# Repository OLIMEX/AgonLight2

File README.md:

# AgonLight2

AgonLight OSHW Retro Z80 computer - an updated version with few updates

This is a re-design of the original version of AgonLight made by Bernardo Kastrup: https://github.com/TheByteAttic/AgonLight

What is new:
- The board schematic and PCB were re-captured and re-layout in KiCad instead of EasyEDA, KiCad is open source software – free to download and use, it is a more fitting CAD tool for an Open Source Hardware project;
- The power of the original AgonLight is delivered through USB-A connector. We decided to replace it with USB-C connector which is used in all new phones, tablets, and devices due to the new EU directive. Usually everyone has such a cable at home to charge and transfer files to their cell phone;
- The linear voltage regulator is replaced with DCDC which delivers up to 2A current;
- Battery Li-Po charger and step-up converter were added, this keeps the board fully operational even if the external power supply gets disconnected;
- The original design has a PS2 connector for a keyboard and required a USB to PS2 adapter to operate with the more available USB keyboards. We replaced the PS2 connector with a USB-A connector so a normal USB keyboard (which supports PS2) can be directly plugged-in to AgonLight;
- AS7C34096A-10TCTR SRAM is routed with 40 ohm impedance lines as per the datasheet;
- Fixed a signal naming in the ESP32-PICO-D4, which now is updated in the original AgonLight documentation;
- The bare header 32-pin connector is replaced with a plastic boxed 34-pin connector following the same layout and adding two additional signals Vbat and Vin which allow AgonLight to be powered via this connector too;
- [UEXT connector](https://www.olimex.com/Products/Modules/UEXT/) was added - it allows AgonLight to be expanded easily (without soldering) with: [temperature sensors, environmental air quality sensors, pressure sensors, humidity sensors, gyroscopes, light sensors, RS485, LCDs, LED matrices, relays, Bluetooth modules, Zigbee modules, Lora modules, GSM modules, RFID readers, GPS, pulse, EKG, RTC, etc](https://www.olimex.com/Products/Modules/);
- Added four 3.3mm mount holes with GND sleeve were added so the board can be attached firmly to a box or another board but also kept the original 2.5mm mount holes.

Please do not forget to check AgonLight topics in GitHub for many utilities and code written by AgonLight community: https://github.com/topics/agon-light

## Useful Agon Resources
- Bernardo Kastrup https://github.com/TheByteAttic/AgonLight
- Dean Belfield Agon VDP, MOS, BBC-BASIC, Agon DOCs, projects https://github.com/breakintoprogram
- Lennart Benschop FORTH, Nano editor and MOS utilities https://github.com/lennart-benschop
- Jeroen Venema Agon Flash, HexLoad, Z80 assembler, tools, sokoban game https://github.com/envenomator
- Mario Smit Agon ZDI Load and tools https://github.com/S0urceror
- Reinhard Schu Agon Assembly https://github.com/schur/Agon-Light-Assembly
- AgonLight emulator https://github.com/james7780/AgonLightEmuSDL
- Alexander Sharikhin MOS tools https://github.com/nihirash/Agon-MOS-Tools
- Nicholas Pratt Agon Game https://github.com/NicholasPratt/Nova-Star
- Robert Lowe Agon Games collection https://github.com/pngwen
- LuzrBum Agon Games https://github.com/LuzrBum

## Licensee
* Hardware is released under CERN Open Hardware Licence Version 2 - Strongly Reciprocal, all silkscreen credits to Bernardo Kastrup and Dean Belfield should remain;
* Software is released under zlib Licensee
* Documentation is released under CC BY-SA 3.0

## Change History

23-04-2023 - Add Resources

14-12-2022 - Initial upload  of CAD files for first prototypes

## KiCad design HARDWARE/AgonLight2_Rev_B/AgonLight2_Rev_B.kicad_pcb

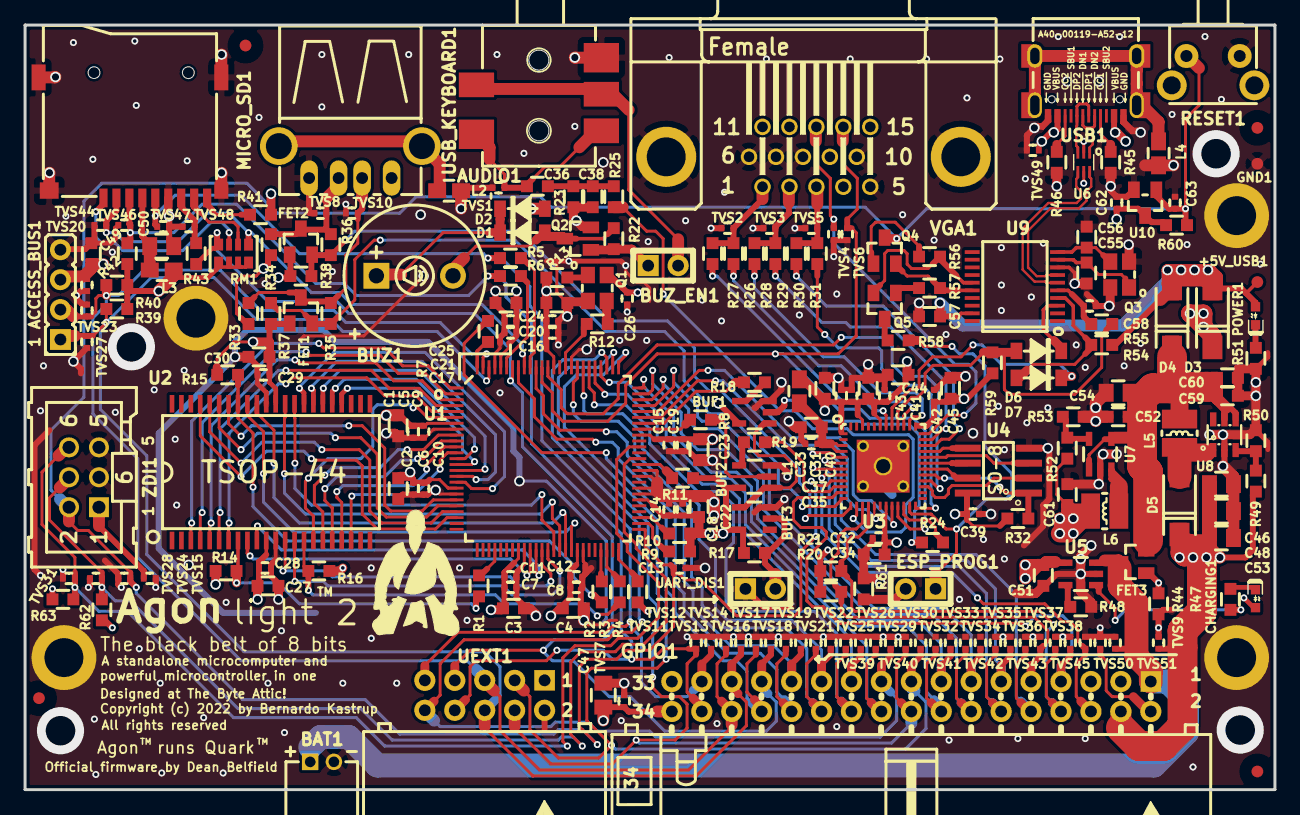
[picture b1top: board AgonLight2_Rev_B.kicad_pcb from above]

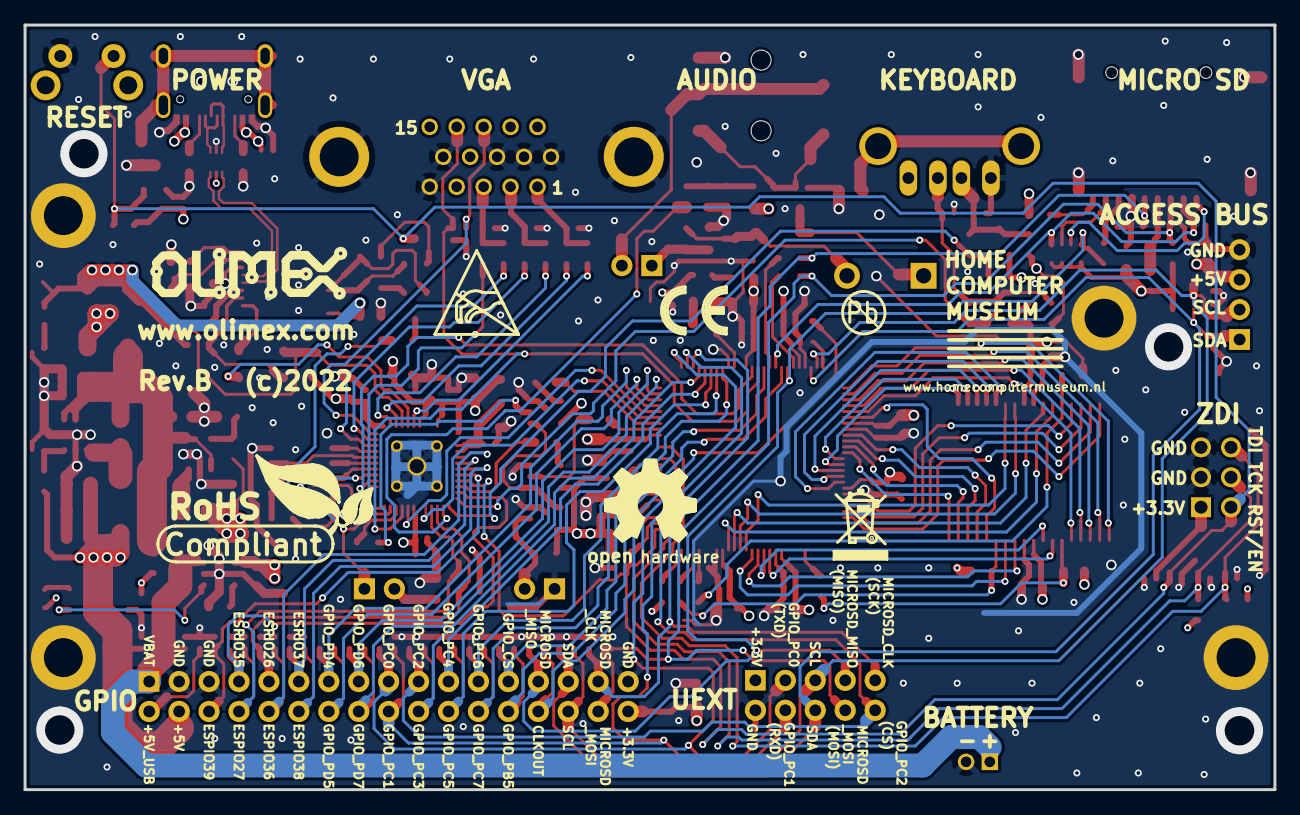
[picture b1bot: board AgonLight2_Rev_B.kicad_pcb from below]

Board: 4 copper layers, 106.1 x 64.9 mm, 247 parts (8 on the bottom side), 157 nets.

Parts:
+5V_USB1: TESTPAD; TP_SMD
ACCESS_BUS1: HN1x4
AUDIO1: PJ-3.5-365-5P(SCJ325P00XG0B02G)-COPY; SCJ325P00XG0B02G
BAT1: DW02R; LIPO_BAT-CON2DW02R
BUF1, BUF2: SN74LVC1G125DBVR; SOT-23-5
BUF3: SN74LVC1G04DBVR(SOT23-5); SOT-23-5
BUZ1: BUZZER_PB1221P(1.1-1.7V_2kHz_12MM); PB1221P_1-Plus_2-Minus
BUZ_EN1: HN1x2+MJ6; HN1x2_Jumper
C1, C2, C3, C4, C22, C23, C24, C25, C27, C30, C33, C34, C36, C37, C43, C44, C45, C49, C59, C60: 10uF/6.3V/20%/X5R/0603; C_0603_5MIL_DWS
C5, C6, C7, C8, C13, C18, C19, C20, C21, C26, C28, C29, C31, C32, C35, C39, C40, C41, C42, C58, C62, C63: 100nF/10V/20%/X5R/0402; C_0402_5MIL_DWS
C9, C10, C11, C12, C14, C15, C16, C17: 1nF/X7R/50VDC/0402; C_0402_5MIL_DWS
C38: 33nF/X7R/50VDC/10%/0603; C_0603_5MIL_DWS
C46, C47, C48, C50, C53, C54: 47uF/6.3V/20%/X5R/0805; C_0805_5MIL_DWS
C51, C52, C57, C61: 22uF/6.3V/20%/X5R/C0603; C_0603_5MIL_DWS
C55, C56: 27pF/C0G/50VDC/5%/0603; C_0603_5MIL_DWS
CHARGING1: LED/YELLOW/0603; LED_0603_KA
D1, D2: 1N4148W/SOD123; SOD-123_1C-2A_KA
D3: NA; SMA-KA
D4, D5: 1N5822/SS34/SMA; SMA-KA
D6, D7: 1N5819S4/SOD123; SOD-123_1C-2A_KA
ESP_PROG1: HN1x2+MJ6; HN1x2_Jumper
FET1, FET2: BSS138(SOT23-3); SOT23
FET3: WPM2015-3/TR; SOT23
FID1, FID2, FID3, FID4: Fiducial; Fiducial1x3
GND1: TESTPAD; TP_SMD
GPIO1: B-R-34-LF(BH34R)2x17_90DEGREE; BH34R
HCM_LOGO: Sign; HomeComputerMuseum2
L1, L2, L3, L4: FB0805/600R/2A; L_0805_5MIL_DWS
L5, L6: 2.2uH/1.5A/NRS3015T2R2MNGH; CD32
Logo_OLIMEX_TB: Logo_OLIMEX_TB
MICRO_SD1: TFC-WPAPR-08-LF; TFC-WPAPR-08
Mounting_hole1, Mounting_hole2, Mounting_hole3, Mounting_hole4: Mounting_hole; Mounting_hole_3.3mm_with_5.5mm_pad
POWER1: LED/RED/0603; LED_0603_KA
Q1: ASE-18.432MHZ-L-C-T; Oscillator-18.432MHz-3.2x2.5mm
Q2, Q4, Q5: BC817-40NPN(SOT23); SOT23
Q3: Q12MHz/20pF/10ppm/4P/3.2x2.5mm; TSX-3.2x2.5mm_GND(3)
R1, R2, R3, R5, R6, R7, R8, R12, R18, R19, R24, R43: 33R/0603; R_0603_5MIL_DWS
R4, R9, R10, R11, R13, R14, R15, R16: 4.7K/0603; R_0603_5MIL_DWS
R17, R32, R33, R34, R42, R44, R54, R55, R60, R61, R62, R63: 10K/0603; R_0603_5MIL_DWS
R20, R21: 22K/0603; R_0603_5MIL_DWS
R22, R37, R38, R39, R40, R47, R48, R51, R56, R57: 2.2K/0603; R_0603_5MIL_DWS
R23: 150R/0603; R_0603_5MIL_DWS
R25: 270R/0603; R_0603_5MIL_DWS
R26, R28, R30: 430R/1%/0603; R_0603_5MIL_DWS
R27, R29, R31: 820R/0603; R_0603_5MIL_DWS
R35, R36: NA(120R/0603); R_0603_5MIL_DWS
R41, R59: NA; R_0603_5MIL_DWS
R45, R46: 5.1K/0603; R_0603_5MIL_DWS
R49: 8.2K/1%/0603; R_0603_5MIL_DWS
R50: 1.1K/1%/0603; R_0603_5MIL_DWS
R52: 220K/0603; R_0603_5MIL_DWS
R53: 49.9K/1%/0603; R_0603_5MIL_DWS
R58: 220R/0603; R_0603_5MIL_DWS
RESET1: B3F-3150; B3F-31XX
RM1: RA1206_(4x0603)_4B8_100k; RA1206_(4X0603)_4B8_xx
Sign_Antistatic: Sign_Antistatic
Sign_CE: CE_Sign
Sign_OSHW_8x8: Sign_OSHW_8x8
Sign_PB-Free: Sign_PB-Free
Sign_RecycleBin_1: Sign_RecycleBin_1
Sign_RoHS_1: Sign_RoHS_1
TVS1, TVS2, TVS3, TVS4, TVS5, TVS6, TVS7, TVS11, TVS12, TVS13, TVS14, TVS15, TVS16, TVS17, TVS18, TVS19, TVS20, TVS21, TVS22, TVS23, TVS24, TVS25, TVS26, TVS27, TVS28, TVS29, TVS30, TVS31, TVS32, TVS33, TVS34, TVS35, TVS36, TVS37, TVS38, TVS39, TVS40, TVS41, TVS42, TVS43, TVS44, TVS45, TVS46, TVS47, TVS48: NA; D_0402_5MIL_DWS
TVS8, TVS9, TVS10, TVS49, TVS50, TVS51: NA(GG0402052R542P); D_0402_5MIL_DWS
U1: EZ80F92AZ020EG(LQFP100); LQFP-100_14x14mm_STM32H730VBT6
U2: AS7C34096A-10TCTR; TSOP-44_Pitch-0.80mm_18.80x11.80x1.20mm
U3: ESP32-PICO-D4
U4: APS6404L-3SQR-SN; SO-8
U5: BL4054B-42TPRN(SOT23-5); SOT-23-5
U6: USBLC6-2P6; SOT-666
U7: SY8089AAAC(SOT23-5); SOT-23-5
U8: MT3608(SOT23-6); SOT23-6
U9: CH340T(SSOP20W); SSOP-20W
U10: VDA2710NTA(SOT-23); SOT-23
UART_DIS1: HN1x2+MJ6; HN1x2_Jumper
UEXT1: B-R-10-LF(BH10R)2x05_90DEGREE; UEXT_BH10R
USB1: USB-C-16P-F(A40-00119-A52-12); USB2.0_TYPE-C(A40-00119-A52-12)
USB_KEYBOARD1: USB-SRWH-4A-LF(USB-A); USB_PN87520_HOST_PTH
VGA1: VGA15; VGA15-F(CD0515S21J0)
ZDI1: BH06S_2x3(B-D-02x3-LF); BH06S

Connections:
+3.3V: BUF1.5, BUF2.5, BUF3.5, C1.1, C2.1, C3.1, C4.1, C5.1, C6.1, C7.1, C8.1, C9.1, C10.1, C11.1, C12.1, C14.1, C15.1, C16.1, C17.1, C18.1, C19.1, C20.1, C21.1, C22.1, C23.1, C24.1, C25.1, C26.1, C27.1, C28.1, C29.1, C30.1, C31.1, C32.1, C33.1, C34.1, C39.2, C40.1, C41.1, C42.1, C43.1, C44.1, C45.1, C47.2, C61.1, C62.1, D2.2, FET1.1, FET2.1, GPIO1.34, L1.1, L3.1, L6.2, Q1.4, R4.1, R9.1, R10.1, R11.1, R13.1, R14.1, R15.1, R16.1, R17.2, R20.1, R21.1, R32.2, R37.2, R38.2, R39.2, R40.2, R41.2, R42.2, R52.2, R59.2, R60.2, R62.2, R63.2, RM1.1.1, RM1.2.1, RM1.3.1, RM1.4.1, TVS7.2, TVS15.2, U1.7, U1.18, U1.33, U1.43, U1.56, U1.67, U1.87, U1.96, U2.11, U2.33, U3.1, U3.19, U3.37, U3.43, U3.46, U4.8, U10.3, UEXT1.1, ZDI1.1
+5V: ACCESS_BUS1.3, C46.2, C48.2, C49.2, C53.2, D3.1, D5.1, GPIO1.4, R33.2, R34.2, R49.1, TVS9.2, TVS20.2, USB_KEYBOARD1.1
+5V_USB: +5V_USB1.1, C51.1, C57.1, CHARGING1.2, D3.2, D4.2, FET3.1, GPIO1.2, POWER1.2, R44.1, R54.1, TVS49.2, TVS50.2, U5.4, U6.5, U9.19, USB1.A4, USB1.A9, USB1.B4, USB1.B9
/BUF1: R18.1, U1.69
/BUF2: BUF2.2, R8.1
/CS: R1.1, R14.2, U2.8
/ESP32-PICO-D4/BUZZER: AUDIO1.4, AUDIO1.5, BUZ_EN1.2
/ESP32-PICO-D4/HS: TVS4.2, U3.36, VGA1.13
/ESP32-PICO-D4/IO4: R31.1, U3.24
/ESP32-PICO-D4/IO5: R30.1, U3.34
/ESP32-PICO-D4/IO18: R29.1, U3.35
/ESP32-PICO-D4/IO19: R28.1, U3.38
/ESP32-PICO-D4/IO21: R27.1, U3.42
/ESP32-PICO-D4/IO22: R26.1, U3.39
/ESP32-PICO-D4/PSRAM_CE: R32.1, U3.29, U4.1
/ESP32-PICO-D4/PSRAM_SCLK: U3.31, U4.6
/ESP32-PICO-D4/PSRAM_SIO0: U3.33, U4.5
/ESP32-PICO-D4/PSRAM_SIO1: U3.27, U4.2
/ESP32-PICO-D4/PSRAM_SIO2: U3.32, U4.3
/ESP32-PICO-D4/PSRAM_SIO3: U3.30, U4.7
/ESP32-PICO-D4/SOUND: R25.2, U3.14
/Power Supply,USB/D+: U6.4, U9.6
/Power Supply,USB/D-: U6.6, U9.7
/Power Supply,USB/DTR: Q5.2, R56.1, U9.15
/Power Supply,USB/RTS: Q4.2, R57.1, U9.16
/RD: R2.1, R15.2, U2.37
/SRAM_A0: U1.1, U2.3
/SRAM_A1: U1.2, U2.4
/SRAM_A2: U1.3, U2.5
/SRAM_A3: U1.4, U2.6
/SRAM_A4: U1.5, U2.7
/SRAM_A5: U1.6, U2.16
/SRAM_A6: U1.9, U2.17
/SRAM_A7: U1.10, U2.18
/SRAM_A8: U1.11, U2.19
/SRAM_A9: U1.12, U2.20
/SRAM_A10: U1.13, U2.27
/SRAM_A11: U1.14, U2.26
/SRAM_A12: U1.15, U2.28
/SRAM_A13: U1.16, U2.29
/SRAM_A14: U1.17, U2.30
/SRAM_A15: U1.20, U2.38
/SRAM_A16: U1.21, U2.39
/SRAM_A17: U1.22, U2.40
/SRAM_A18: U1.23, U2.41
/SRAM_DATA0: U1.35, U2.9
/SRAM_DATA1: U1.36, U2.10
/SRAM_DATA2: U1.37, U2.13
/SRAM_DATA3: U1.38, U2.14
/SRAM_DATA4: U1.39, U2.31
/SRAM_DATA5: U1.40, U2.32
/SRAM_DATA6: U1.41, U2.35
/SRAM_DATA7: U1.42, U2.36
/WR: R3.1, R16.2, U2.15
CLKOUT: GPIO1.28, R7.2, TVS16.2
ESP32_CTS: U1.71, U3.20
ESP32_RTS: U1.70, U3.17
ESPIO26: GPIO1.9, R20.2, TVS41.2, U3.15
ESPIO27: GPIO1.8, R21.2, TVS42.2, U3.16
ESPIO35: GPIO1.7, TVS43.2, U3.11
ESPIO36: GPIO1.10, TVS40.2, U3.5
ESPIO37: GPIO1.11, TVS39.2, U3.6
ESPIO38: GPIO1.12, TVS38.2, U3.7
ESPIO39: GPIO1.6, TVS45.2, U3.8
ESP_CH340_RXD: D6.2, R55.2, R59.1, U3.40
ESP_CH340_TXD: D7.1, U3.41
ESP_RXD: R19.1, U3.10
ESP_TXD: BUF1.2, R24.1
GND: ACCESS_BUS1.4, AUDIO1.2, BAT1.2, BUF1.3, BUF2.3, BUF3.3, C1.2, C2.2, C3.2, C4.2, C5.2, C6.2, C7.2, C8.2, C9.2, C10.2, C11.2, C12.2, C13.2, C14.2, C15.2, C16.2, C17.2, C18.2, C19.2, C20.2, C21.2, C22.2, C23.2, C24.2, C25.2, C26.2, C27.2, C28.2, C29.2, C30.2, C31.2, C32.2, C33.2, C34.2, C35.2, C37.2, C38.1, C39.1, C40.2, C41.2, C42.2, C43.2, C44.2, C45.2, C46.1, C47.1, C48.1, C49.1, C50.2, C51.2, C52.2, C53.1, C54.1, C55.2, C56.2, C57.2, C58.2, C59.1, C60.1, C61.2, C62.2, C63.1, GND1.1, GPIO1.3, GPIO1.5, GPIO1.33, L2.2, L4.2, MICRO_SD1.6, MICRO_SD1.10, MICRO_SD1.11, MICRO_SD1.12, MICRO_SD1.13, Mounting_hole1.0, Mounting_hole2.0, Mounting_hole3.0, Mounting_hole4.0, Q1.2, Q2.2, Q3.3, R23.2, R44.2, R45.2, R46.2, R48.2, R50.2, R51.2, R53.2, R61.2, RESET1.1, TVS1.1, TVS2.1, TVS3.1, TVS4.1, TVS5.1, TVS6.1, TVS7.1, TVS8.1, TVS9.1, TVS10.1, TVS11.1, TVS12.1, TVS13.1, TVS14.1, TVS15.1, TVS16.1, TVS17.1, TVS18.1, TVS19.1, TVS20.1, TVS21.1, TVS22.1, TVS23.1, TVS24.1, TVS25.1, TVS26.1, TVS27.1, TVS28.1, TVS29.1, TVS30.1, TVS31.1, TVS32.1, TVS33.1, TVS34.1, TVS35.1, TVS36.1, TVS37.1, TVS38.1, TVS39.1, TVS40.1, TVS41.1, TVS42.1, TVS43.1, TVS44.1, TVS45.1, TVS46.1, TVS47.1, TVS48.1, TVS49.1, TVS50.1, TVS51.1, U1.8, U1.19, U1.34, U1.44, U1.57, U1.58, U1.60, U1.61, U1.84, U1.97, U2.12, U2.34, U3.49, U4.4, U5.2, U6.2, U7.2, U8.2, U9.8, U10.2, UART_DIS1.1, UEXT1.2, USB1.A1, USB1.A12, USB1.B1, USB1.B12, USB_KEYBOARD1.4, VGA1.5, VGA1.6, VGA1.7, VGA1.8, VGA1.10, VGA1.16, VGA1.17, ZDI1.3, ZDI1.5
GPIO_CS: GPIO1.25, TVS19.2, U1.90
GPIO_PB5: GPIO1.26, TVS18.2, U1.93
GPIO_PC0: GPIO1.17, TVS33.2, U1.76, UEXT1.3
GPIO_PC1: GPIO1.18, TVS32.2, U1.77, UEXT1.4
GPIO_PC2: GPIO1.19, TVS30.2, U1.78, UEXT1.10
GPIO_PC3: GPIO1.20, TVS29.2, U1.79
GPIO_PC4: GPIO1.21, TVS26.2, U1.80
GPIO_PC5: GPIO1.22, TVS25.2, U1.81
GPIO_PC6: GPIO1.23, TVS22.2, U1.82
GPIO_PC7: GPIO1.24, TVS21.2, U1.83
GPIO_PD4: GPIO1.13, TVS37.2, U1.72
GPIO_PD5: GPIO1.14, TVS36.2, U1.73
GPIO_PD6: GPIO1.15, TVS35.2, U1.74
GPIO_PD7: GPIO1.16, TVS34.2, U1.75
IO0: ESP_PROG1.1, R58.2, U3.23
ITRP: U1.88, U3.28
KCLK: FET2.2, R36.2, R38.1, U3.13
KDAT: FET1.2, R35.2, R37.1, U3.12
MICROSD_CLK: GPIO1.31, MICRO_SD1.5, R5.2, TVS12.2, TVS47.2, UEXT1.9
MICROSD_CS: MICRO_SD1.2, RM1.4.2, TVS44.2, U1.92
MICROSD_MISO: GPIO1.27, R43.2, RM1.1.2, TVS17.2, U1.94, UEXT1.7
MICROSD_MOSI: GPIO1.32, MICRO_SD1.3, R6.2, R42.1, TVS11.2, TVS46.2, UEXT1.8
unnamed: AUDIO1.1, AUDIO1.3, C36.2, TVS1.2
unnamed: BUF1.1, BUF2.1, BUF3.4
unnamed: BUF1.4, R18.2
unnamed: BUF2.4, R19.2
unnamed: BUF3.2, R17.1, UART_DIS1.2
unnamed: BUZ1.1, D1.1, D2.1
unnamed: BUZ1.2, D1.2, Q2.3, R22.2
unnamed: BUZ_EN1.1, Q2.1, R22.1
unnamed: C35.1, C37.1, L1.2, U3.3, U3.4
unnamed: C36.1, C38.2, R23.1, R25.1
unnamed: C50.1, L3.2, MICRO_SD1.4
unnamed: C52.1, C54.2, C59.2, C60.2, D4.1, FET3.2, L5.2, U7.1, U7.4, U8.4, U8.5
unnamed: C55.1, Q3.1, U9.9
unnamed: C56.1, Q3.2, U9.10
unnamed: C58.1, R55.1, U9.5
unnamed: CHARGING1.1, R47.1
unnamed: D5.2, L5.1, U8.1
unnamed: D6.1, U9.3
unnamed: D7.2, R54.2, U9.4
unnamed: ESP_PROG1.2, R61.1
unnamed: FET1.3, R33.1, R35.1, TVS10.2, USB_KEYBOARD1.2
unnamed: FET2.3, R34.1, R36.1, TVS8.2, USB_KEYBOARD1.3
unnamed: L2.1, USB_KEYBOARD1.5
unnamed: L4.1, USB1.0
unnamed: L6.1, U7.3
unnamed: MICRO_SD1.1, RM1.2.2
unnamed: MICRO_SD1.7, R43.1, TVS48.2
unnamed: MICRO_SD1.8, RM1.3.2
unnamed: MICRO_SD1.9, R41.1
unnamed: POWER1.1, R51.1
unnamed: Q1.1, R13.2
unnamed: Q1.3, R12.1
unnamed: Q4.1, R56.2
unnamed: Q5.1, R57.2
unnamed: Q5.3, R58.1
unnamed: R1.2, U1.29
unnamed: R2.2, U1.47
unnamed: R3.2, U1.48
unnamed: R4.2, U1.50
unnamed: R5.1, U1.91
unnamed: R6.1, U1.95
unnamed: R7.1, U1.100
unnamed: R8.2, U1.68
unnamed: R9.2, U1.52
unnamed: R10.2, U1.53
unnamed: R11.2, U1.62
unnamed: R12.2, U1.85
unnamed: R24.2, U3.22
unnamed: R26.2, R27.2, TVS2.2, VGA1.1
unnamed: R28.2, R29.2, TVS3.2, VGA1.2
unnamed: R30.2, R31.2, TVS5.2, VGA1.3
unnamed: R45.1, USB1.A5
unnamed: R46.1, USB1.B5
unnamed: R47.2, U5.1
unnamed: R48.1, U5.5
unnamed: R49.2, R50.1, U8.3
unnamed: R52.1, R53.1, U7.5
unnamed: U6.1, USB1.A7, USB1.B7
unnamed: U6.3, USB1.A6, USB1.B6
RST\EN: C13.1, C63.2, Q4.3, R60.1, RESET1.2, TVS24.2, U1.51, U3.9, U10.1, ZDI1.2
SCL: ACCESS_BUS1.2, GPIO1.30, R40.1, TVS13.2, TVS23.2, U1.99, UEXT1.5
SDA: ACCESS_BUS1.1, GPIO1.29, R39.1, TVS14.2, TVS27.2, U1.98, UEXT1.6
TCK: R62.1, TVS28.2, U1.63, ZDI1.4
TDI: R63.1, TVS31.2, U1.65, ZDI1.6
VBAT: BAT1.1, FET3.3, GPIO1.1, TVS51.2, U5.3
VS: TVS6.2, U1.89, U3.21, VGA1.14

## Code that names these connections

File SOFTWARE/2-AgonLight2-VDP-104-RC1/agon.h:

//
// Title:	        Agon Video BIOS - Function prototypes
// Author:        	Dean Belfield
// Created:       	05/09/2022
// Last Updated:    23/03/2023
//
// Modinfo:
// 04/03/2023:      Added LOGICAL_SCRW and LOGICAL_SCRH
// 17/03/2023:		Added PACKET_RTC, EPOCH_YEAR, MAX_SPRITES, MAX_BITMAPS
// 21/03/2023:		Added PACKET_KEYSTATE
// 22/03/2023:		Added VDP codes
// 23/03/2023:		Increased baud rate to 1152000

#pragma once

#define	ESPSerial Serial2

#define USE_HWFLOW				1		// Flow Control: 1 = enable hardware flow control to eZ80

#define EPOCH_YEAR				1980	// 1-byte dates are offset from this (for FatFS)
#define MAX_SPRITES				256		// Maximum number of sprites
#define MAX_BITMAPS				256		// Maximum number of bitmaps

#define UART_BR					1152000	// Max baud rate; previous stable value was 384000
#define UART_NA					-1
#define UART_TX					2
#define UART_RX					34
#define UART_RTS  	 		 	13 		// The ESP32 RTS pin (eZ80 CTS)
#define UART_CTS  	  			14		// The ESP32 CTS pin (eZ80 RTS)

#define UART_RX_SIZE			256		// The RX buffer size
#define UART_RX_THRESH			128		// Point at which RTS is toggled

#define GPIO_ITRP				17		// VSync Interrupt Pin - for reference only

// Commands for VDU 23, 0, n
//
#define VDP_GP					0x80	// General poll data
#define VDP_KEYCODE				0x81	// Keyboard data
#define VDP_CURSOR				0x82	// Cursor positions
#define VDP_SCRCHAR				0x83	// Character read from screen
#define VDP_SCRPIXEL			0x84	// Pixel read from screen
#define VDP_AUDIO				0x85	// Audio acknowledgement
#define VDP_MODE				0x86	// Get screen dimensions
#define VDP_RTC					0x87	// RTC
#define VDP_KEYSTATE			0x88	// Keyboard repeat rate and LED status
#define VDP_LOGICALCOORDS		0xC0	// Switch BBC Micro style logical coords on and off
#define VDP_TERMINALMODE		0xFF	// Switch to terminal mode

// And the corresponding return packets
// By convention, these match their VDP counterpart, but with the top bit reset
//
#define PACKET_GP				0x00	// General poll data
#define PACKET_KEYCODE			0x01	// Keyboard data
#define PACKET_CURSOR			0x02	// Cursor positions
#define PACKET_SCRCHAR			0x03	// Character read from screen
#define PACKET_SCRPIXEL			0x04	// Pixel read from screen
#define PACKET_AUDIO			0x05	// Audio acknowledgement
#define PACKET_MODE				0x06	// Get screen dimensions
#define PACKET_RTC				0x07	// RTC
#define PACKET_KEYSTATE			0x08	// Keyboard repeat rate and LED status

#define AUDIO_CHANNELS			3		// Number of audio channels
#define PLAY_SOUND_PRIORITY 	3		// Sound driver task priority with 3 (configMAX_PRIORITIES - 1) being the highest, and 0 being the lowest

#define LOGICAL_SCRW            1280    // As per the BBC Micro standard
#define LOGICAL_SCRH            1024

#if CONFIG_FREERTOS_UNICORE
#define ARDUINO_RUNNING_CORE	0
#else
#define ARDUINO_RUNNING_CORE	1
#endif

// Function Prototypes
//
void debug_log(const char *format, ...);

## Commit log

2022-12-14 Initial upload CAD files
2023-01-06 add user manual
2023-04-14 Update README.md
    add Agon-Light GitHub Topics link
2023-04-22 Update Readme with resources
2023-06-06 Update
    Added 1.04 basic, added new examples, updated structure
2023-06-07 Update SD card content
    Added CP/M (original source: https://github.com/nihirash/Agon-CPM2.2 ).
    MOS update firmware file moved into the mos directory and updated readme file.
    Renamed folder of the Olimex challenges
2023-06-09 Update
    Manual and directory structure
2023-06-09 Update
    Directory structure
2023-06-09 Updated examples
    Added solutions for the 3rd Olimex Weekly Programming Challenge (snake).
    Added various 3rd party examples
2023-06-09 Update
    revision B
2023-07-05 Update
    UM update
2023-07-12 added gitattributes
    github trunks cr, this forces both crlf
2023-07-12 Update
    relocated gittatributes to proper location
2023-07-12 Updated VDP and MOS to 1.04, and BASIC to 1.05
    Taken a snapshot of the Release-Candidate-1 of the agon-vdp, agon-mos and the binary of agon-bbc-basic from Dean Belfield (https://github.com/breakintoprogram) replacing the old versions.
2023-07-12 Update manual
2023-08-22 Update
    Minor manual update
2023-10-26 Update
    Added dimensions
2023-10-27 Update
    Added dimension link in the manual
2024-03-21 user manual update
2024-03-21 Update README.md
    Notice about ESP32 package 3.x.x
2024-03-21 Updated VDP, MOS and BASIC to the latest versions
    VDP and MOS updated from 1.04-rc1 to 1.04 (thanks to Dean Belfield - breakintoprogram)
    Changed Arduino project for the VDP, MOS project for ZDS2 IDE.
    BASIC updated from 1.05 to 1.06 version.
    The bin file in the SD card content has been changed to the latest one.
    Added latest MOS file in the SD card files.
    Added updater for the VDP using only bin files (thanks to Jeroen Venema - envenomator)
2024-03-21 Update README.md
    Update
2024-06-14 Update
    Added console8 upgrade directory with all required files and instructions.

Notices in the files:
HARDWARE/AgonLight2_Rev_B/AgonLight2_Rev_B.kicad_pcb:
(c)2022
All rights reserved
Copyright (c) 2022 by Bernardo Kastrup
